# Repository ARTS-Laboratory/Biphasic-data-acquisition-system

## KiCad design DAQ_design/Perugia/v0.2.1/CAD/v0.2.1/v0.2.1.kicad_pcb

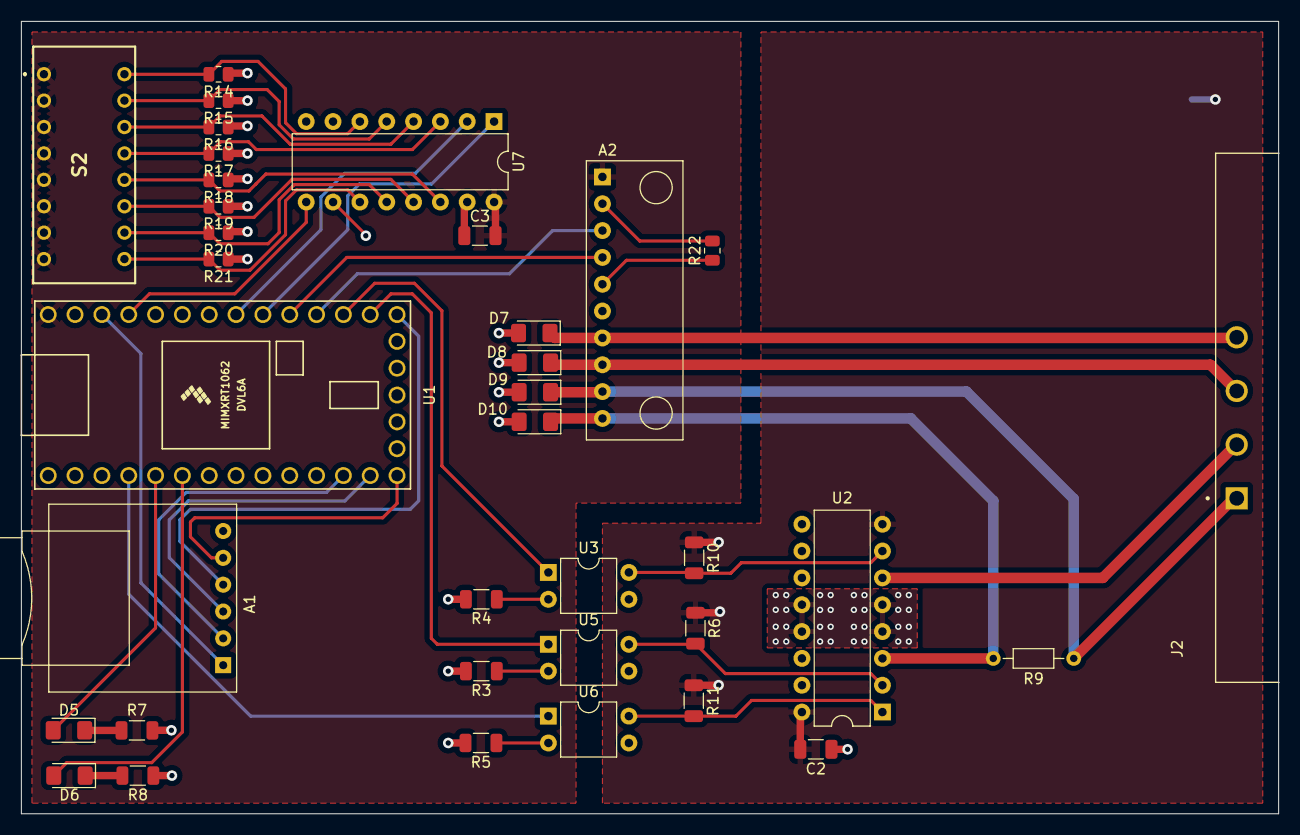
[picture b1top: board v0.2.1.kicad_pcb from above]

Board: 4 copper layers, 119.0 x 75.0 mm, 37 parts (1 on the bottom side), 41 nets.

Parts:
A1: SD_Card_Module
A2: ADS1115_ADC_Module; ADC1115_ADC_Module
BT1: Battery; JST_GH_SM02B-GHS-TB_1x02-1MP_P1.25mm_Horizontal
C2, C3: 0.1uf; C_1206_3216Metric
D5, D6: LED; LED_1206_3216Metric_Pad1.42x1.75mm_HandSolder
D7: zener1; D_1206_3216Metric_Pad1.42x1.75mm_HandSolder
D8: zener2; D_1206_3216Metric_Pad1.42x1.75mm_HandSolder
D9: zener3; D_1206_3216Metric_Pad1.42x1.75mm_HandSolder
D10: zener4; D_1206_3216Metric_Pad1.42x1.75mm_HandSolder
J2: 1899003; PHOENIX_1899003
R3, R4, R5: 470; R_1206_3216Metric
R6, R10, R11: 10k; R_1206_3216Metric
R7, R8: 260; R_1206_3216Metric
R9: R_Small; R_Axial_DIN0204_L3.6mm_D1.6mm_P7.62mm_Horizontal
R14, R15, R16, R17, R18, R19, R20, R21, R22: 10k; R_0805_2012Metric
S2: 76PSB08ST
U1: Teensy4.0; Teensy40
U2: L293D; DIP-16_W7.62mm
U3, U5, U6: PC817; DIP-4_W7.62mm
U7: 74HC165; DIP-16_W7.62mm

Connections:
+3.3V: A1.1 (3V3), U1.31 (3V3)
ADC_SCL: A2.3 (SCL), U1.23 (16_A2_RX4_SCL1)
ADC_SDA: A2.4 (SDA), U1.24 (17_A3_TX4_SDA1)
DIPCP: U1.26 (19_A5_SCL0), U7.2 (CP)
DIPDAT: U1.30 (23_A9_CRX1_MCLK1), U7.9 (Q7)
DIPLAT: U1.25 (18_A4_SDA0), U7.1 (~PL)
EN: U1.4 (2_OUT2), U6.1
EX+: A2.10 (A3), D10.1 (K), R9.2, U2.3 (1Y)
EX-: J2.2, U2.6 (2Y)
GND: BT1.2 (-), C2.1, U2.4 (GND), U2.5 (GND), U2.12 (GND), U2.13 (GND), U3.3, U5.3, U6.3
GNDD: A1.6 (GND), A2.2 (GND), C3.1, D7.2 (A), D8.2 (A), D9.2 (A), D10.2 (A), R3.2, R4.2, R5.2, R7.1, R8.1, R14.1, R15.1, R16.1, R17.1, R18.1, R19.1, R20.1, R21.1, R22.2, U1.1 (GND), U1.32 (GND), U7.8 (GND), U7.10 (DS), U7.15 (~CE)
IN1: A2.9 (A2), D9.1 (K), J2.1, R9.1
IN2: A2.7 (A0), D7.1 (K), J2.4
IN3: A2.8 (A1), D8.1 (K), J2.3
LEDACT: D6.2 (A), U1.6 (4_BCLK2)
LEDPOW: D5.2 (A), U1.5 (3_LRCLK2)
LOGIC1: U1.21 (14_A0_TX3_SPDIF_OUT), U5.1
LOGIC2: U1.22 (15_A1_RX3_SPDIF_IN), U3.1
unnamed: A2.5 (ADDR), R22.1
unnamed: D5.1 (K), R7.2
unnamed: D6.1 (K), R8.2
unnamed: R3.1, U5.2
unnamed: R4.1, U3.2
unnamed: R5.1, U6.2
OPT1: R6.2, U2.2 (1A), U5.4
OPT2: R10.2, U2.7 (2A), U3.4
OPTEN: R11.2, U2.1 (EN1,2), U6.4
SDCLK: A1.4 (CLK), U1.20 (13_SCK_CRX1_LED)
SDCS: A1.2 (CS), U1.12 (10_CS_MQSR)
SDMISO: A1.5 (MISO), U1.14 (12_MISO_MQSL)
SDMOSI: A1.3 (MOSI), U1.13 (11_MOSI_CTX1)
SW1: R21.2, S2.B8 (COM_8), U7.11 (D0)
SW2: R20.2, S2.B7 (COM_7), U7.12 (D1)
SW3: R19.2, S2.B6 (COM_6), U7.13 (D2)
SW4: R18.2, S2.B5 (COM_5), U7.14 (D3)
SW5: R17.2, S2.B4 (COM_4), U7.3 (D4)
SW6: R16.2, S2.B3 (COM_3), U7.4 (D5)
SW7: R15.2, S2.B2 (COM_2), U7.5 (D6)
SW8: R14.2, S2.B1 (COM_1), U7.6 (D7)
VDD: A2.1 (VCC), C3.2, S2.A1 (NC_1), S2.A2 (NC_2), S2.A3 (NC_3), S2.A4 (NC_4), S2.A5 (NC_5), S2.A6 (NC_6), S2.A7 (NC_7), S2.A8 (NC_8), U1.33 (VIN), U7.16 (VCC)
VPP: BT1.1 (+), C2.2, R6.1, R10.1, R11.1, U2.8 (VCC2), U2.16 (VCC1)

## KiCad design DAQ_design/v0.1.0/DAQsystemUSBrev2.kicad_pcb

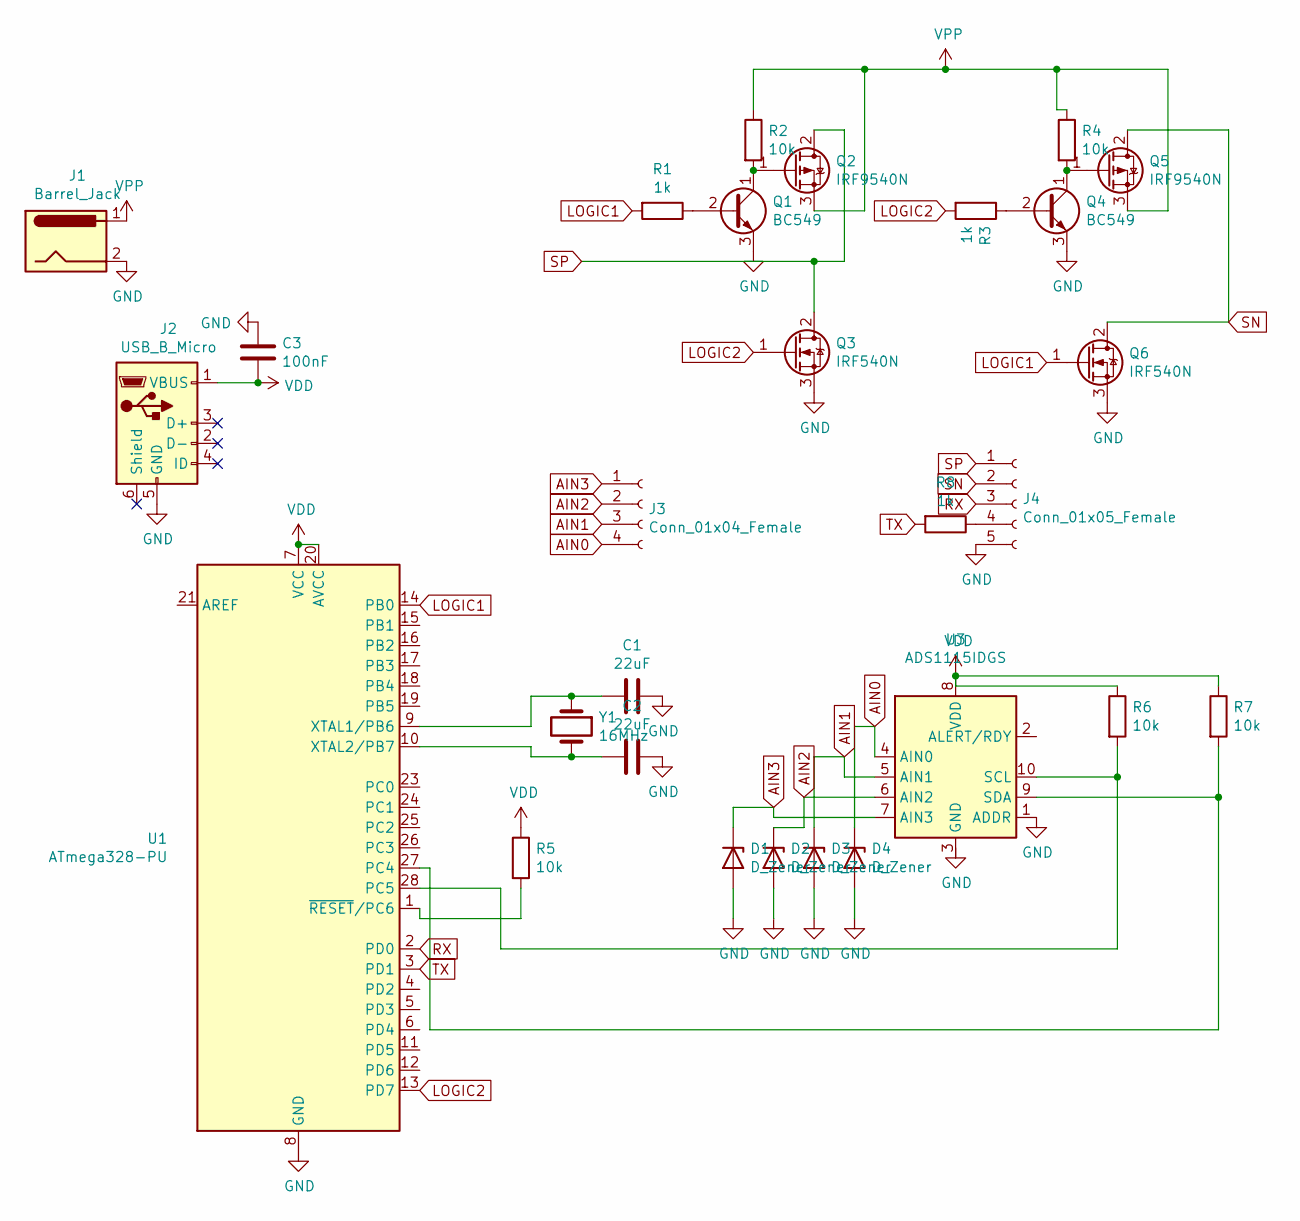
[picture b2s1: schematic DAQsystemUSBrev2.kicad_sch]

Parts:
C1, C2: 22uF; C_Disc_D5.0mm_W2.5mm_P5.00mm
C3: 100nF; C_0603_1608Metric
D1, D2, D3, D4: D_Zener; D_DO-35_SOD27_P7.62mm_Horizontal
J1: Barrel_Jack; BarrelJack_Horizontal
J2: USB_B_Micro; USB_Micro-B_Molex-105017-0001
J3: Conn_01x04_Female; PinSocket_1x04_P2.54mm_Vertical
J4: Conn_01x05_Female; PinSocket_1x05_P2.54mm_Vertical
Q1, Q4: BC549; TO-92_Inline_Wide
Q2, Q5: IRF9540N; TO-220-3_Vertical
Q3, Q6: IRF540N; TO-220-3_Vertical
R1, R3, R8: 1k; R_0603_1608Metric
R2, R4, R5, R6, R7: 10k; R_0603_1608Metric
U1: ATmega328-PU; DIP-28_W7.62mm
U3: ADS1115IDGS; TSSOP-10_3x3mm_P0.5mm
Y1: 16MHz; Crystal_HC49-U_Vertical

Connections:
AIN0: D4.1 (K), J3.4, U3.4 (AIN0)
AIN1: D3.1 (K), J3.3, U3.5 (AIN1)
AIN2: D2.1 (K), J3.2, U3.6 (AIN2)
AIN3: D1.1 (K), J3.1, U3.7 (AIN3)
GND: C1.1, C2.1, C3.1, D1.2 (A), D2.2 (A), D3.2 (A), D4.2 (A), J1.2, J2.5 (GND), J4.5, Q1.3 (E), Q3.3 (S), Q4.3 (E), Q6.3 (S), U1.8 (GND), U1.22 (GND), U3.1 (ADDR)
LOGIC1: Q6.1 (G), R1.2, U1.14 (PB0)
LOGIC2: Q3.1 (G), R3.2, U1.13 (PD7)
unnamed: C1.2, U1.9 (XTAL1/PB6), Y1.1
unnamed: C2.2, U1.10 (XTAL2/PB7), Y1.2
unnamed: J4.4, R8.1
unnamed: Q1.1 (C), Q2.1 (G), R2.2
unnamed: Q1.2 (B), R1.1
unnamed: Q4.1 (C), Q5.1 (G), R4.2
unnamed: Q4.2 (B), R3.1
unnamed: R5.2, U1.1 (~RESET/PC6)
unnamed: R6.2, U1.28 (PC5), U3.10 (SCL)
unnamed: R7.2, U1.27 (PC4), U3.9 (SDA)
RX: J4.3, U1.2 (PD0)
SN: J4.2, Q5.2 (D), Q6.2 (D)
SP: J4.1, Q2.2 (D), Q3.2 (D)
TX: R8.2, U1.3 (PD1)
VDD: C3.2, J2.1 (VBUS), R5.1, R6.1, R7.1, U1.7 (VCC), U1.20 (AVCC), U3.8 (VDD)
VPP: J1.1, Q2.3 (S), Q5.3 (S), R2.1, R4.1

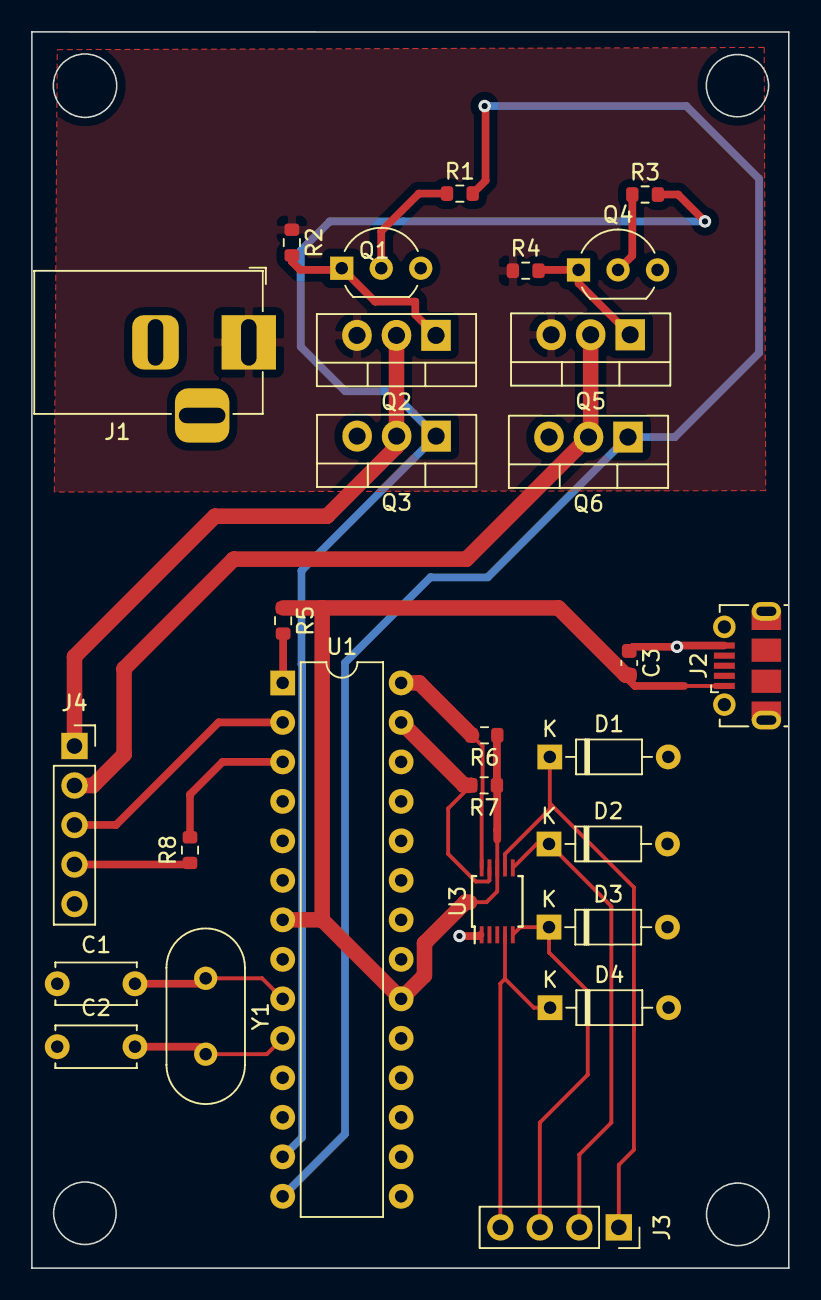
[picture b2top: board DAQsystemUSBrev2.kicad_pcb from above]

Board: 2 copper layers, 48.7 x 79.5 mm, 28 parts (0 on the bottom side), 23 nets.

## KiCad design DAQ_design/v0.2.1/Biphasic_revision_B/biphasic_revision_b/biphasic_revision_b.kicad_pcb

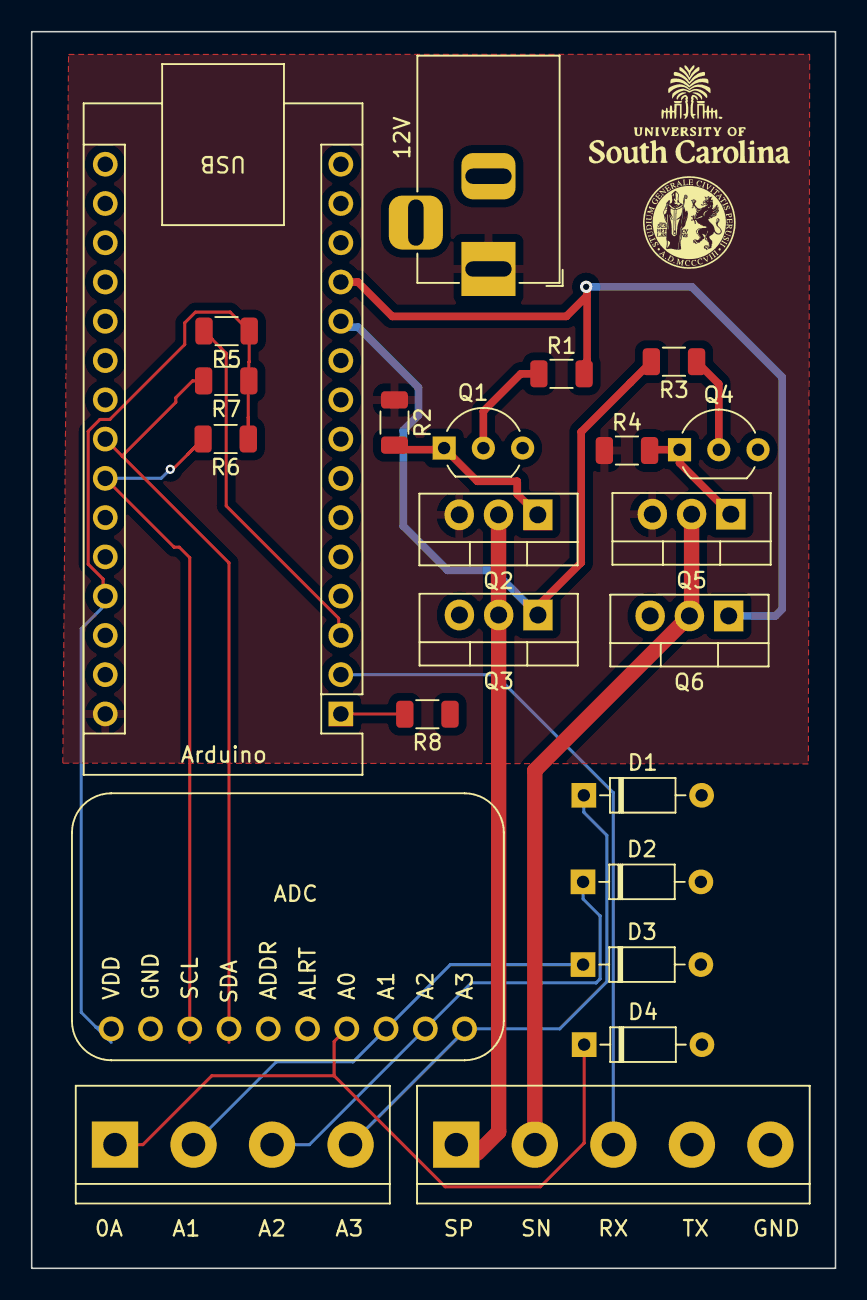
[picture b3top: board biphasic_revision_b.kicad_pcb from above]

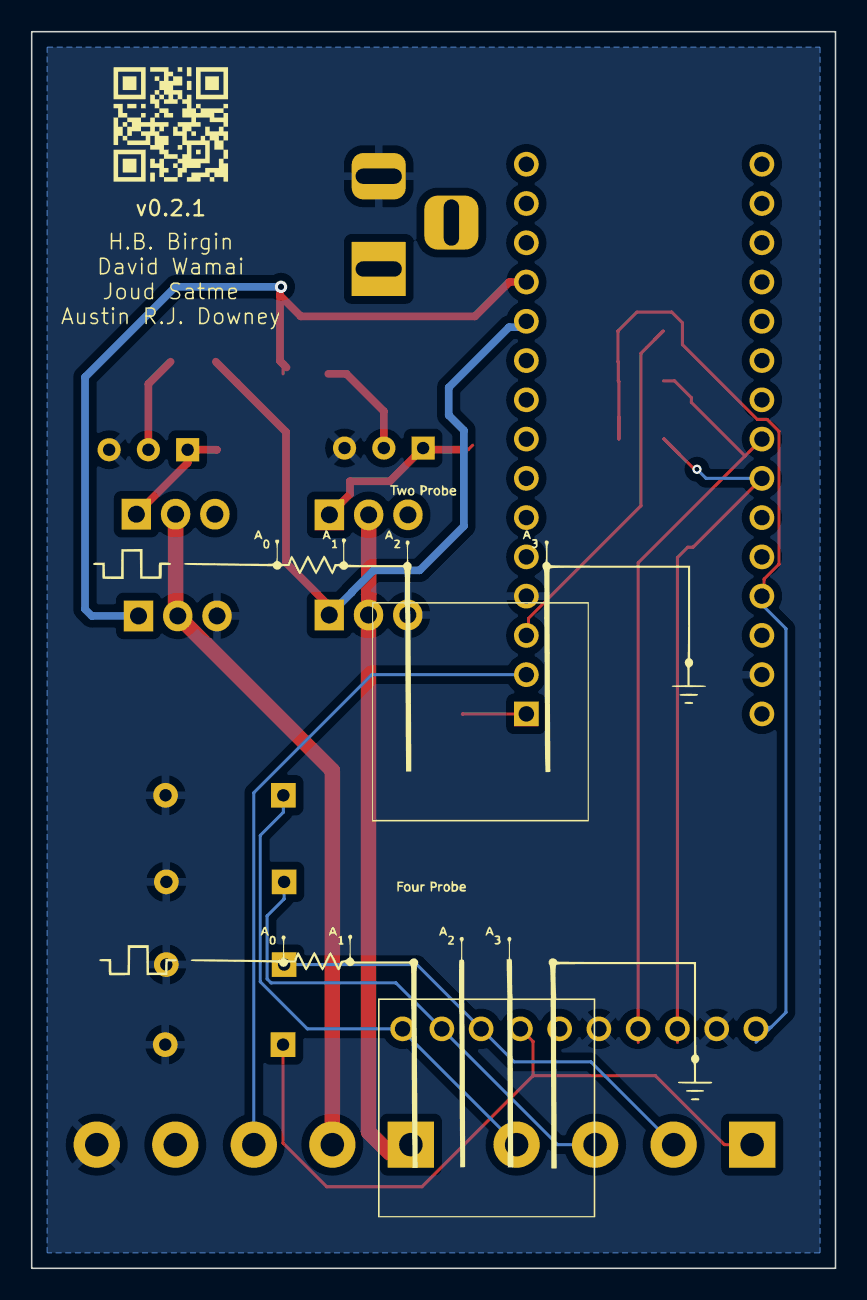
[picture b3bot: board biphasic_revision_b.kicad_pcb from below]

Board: 2 copper layers, 52.0 x 80.0 mm, 27 parts (2 on the bottom side), 20 nets.

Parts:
A1: Arduino_Nano_Every; Arduino_Nano
Analog_In1: Screw_Terminal_01x04; TerminalBlock_bornier-4_P5.08mm
D1, D2, D3, D4: D_Zener; D_DO-35_SOD27_P7.62mm_Horizontal
G2: LOGO; uofsc
G3: LOGO; upg
G5: LOGO; schematic
G7: LOGO; github
J1: Barrel_Jack; BarrelJack_Horizontal
J3: Screw_Terminal_01x05; TerminalBlock_bornier-5_P5.08mm
Q1, Q4: BC549; TO-92_Inline_Wide
Q2, Q5: IRF9540N; TO-220-3_Vertical
Q3, Q6: IRF540N; TO-220-3_Vertical
R1, R3, R8: 1k; R_1206_3216Metric
R2, R4, R5, R6, R7: 10k; R_1206_3216Metric
U3: ADS1115IDGS; Adafruit_ADS1115

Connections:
AIN0: Analog_In1.1, D4.1 (K), U3.7 (AIN0)
AIN1: Analog_In1.2, D3.1 (K), U3.8 (AIN1)
AIN2: Analog_In1.3, D2.1 (K), U3.9 (AIN2)
AIN3: Analog_In1.4, D1.1 (K), U3.10 (AIN3)
GND: A1.4 (GND), A1.29 (GND), D1.2 (A), D2.2 (A), D3.2 (A), D4.2 (A), J1.2, J3.5, Q1.3 (E), Q3.3 (S), Q4.3 (E), Q6.3 (S), U3.2 (GND), U3.5 (ADDR)
LOGIC1: A1.12 (D9), Q6.1 (G), R1.2
LOGIC2: A1.11 (D8), Q3.1 (G), R3.2
unnamed: A1.24 (SCL/A5), R6.2, U3.3 (SCL)
unnamed: A1.23 (SDA/A4), R7.2, U3.4 (SDA)
unnamed: A1.3 (~RESET), R5.2
unnamed: Q1.2 (B), R1.1
unnamed: Q1.1 (C), Q2.1 (G), R2.2
unnamed: Q4.2 (B), R3.1
unnamed: Q4.1 (C), Q5.1 (G), R4.2
RX: A1.2 (RX1), J3.3
SN: J3.2, Q5.2 (D), Q6.2 (D)
SP: J3.1, Q2.2 (D), Q3.2 (D)
TX: A1.1 (TX1), R8.2
VDD: A1.27 (+5V), R5.1, R6.1, R7.1, U3.1 (VDD)
VPP: A1.30 (VIN), J1.1, Q2.3 (S), Q5.3 (S), R2.1, R4.1
